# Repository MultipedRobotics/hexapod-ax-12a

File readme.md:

# Hexapod

*in process*

## Others

- Kevin Ochs [ROS1 Hexapod](https://github.com/KevinOchs/hexapod_ros)
    - 
- Razbotics [ROS1 Hexapod](https://github.com/Razbotics/hexapod_ros)
    - This is a fork of Kevin Ochs' hexapod
    - 
- Emiliano Borghi [ROS1 Crab](https://github.com/eborghi10/Hexapod-ROS)
- Biriuk Ivan [ROS1 Crab](http://wiki.ros.org/Robots/HexapodRobot)
    - 
- Davis Weis [ROS1 Hopper](https://github.com/dmweis/Hopper_ROS)
    - 
- Unknown 
    - 

# MIT License

**Copyright (c) 2020 Kevin J. Walchko**

Permission is hereby granted, free of charge, to any person obtaining a copy
of this software and associated documentation files (the "Software"), to deal
in the Software without restriction, including without limitation the rights
to use, copy, modify, merge, publish, distribute, sublicense, and/or sell
copies of the Software, and to permit persons to whom the Software is
furnished to do so, subject to the following conditions:

The above copyright notice and this permission notice shall be included in all
copies or substantial portions of the Software.

THE SOFTWARE IS PROVIDED "AS IS", WITHOUT WARRANTY OF ANY KIND, EXPRESS OR
IMPLIED, INCLUDING BUT NOT LIMITED TO THE WARRANTIES OF MERCHANTABILITY,
FITNESS FOR A PARTICULAR PURPOSE AND NONINFRINGEMENT. IN NO EVENT SHALL THE
AUTHORS OR COPYRIGHT HOLDERS BE LIABLE FOR ANY CLAIM, DAMAGES OR OTHER
LIABILITY, WHETHER IN AN ACTION OF CONTRACT, TORT OR OTHERWISE, ARISING FROM,
OUT OF OR IN CONNECTION WITH THE SOFTWARE OR THE USE OR OTHER DEALINGS IN THE
SOFTWARE.

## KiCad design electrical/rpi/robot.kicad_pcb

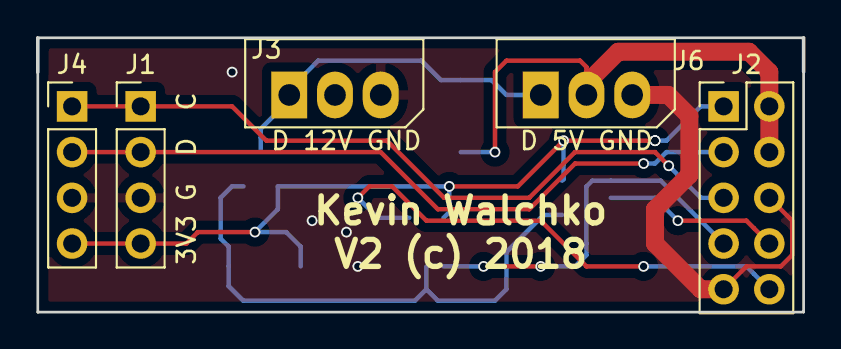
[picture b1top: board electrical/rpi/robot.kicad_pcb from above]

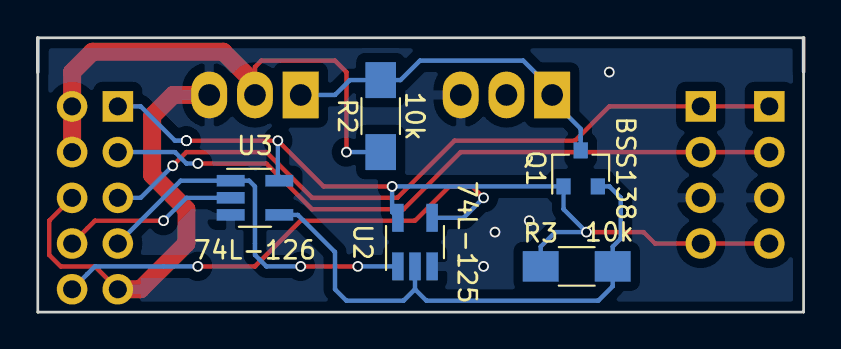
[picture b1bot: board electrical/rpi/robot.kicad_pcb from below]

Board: 2 copper layers, 42.5 x 15.2 mm, 10 parts (5 on the bottom side), 10 nets.

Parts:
J1, J4: i2c; Pin_Header_Straight_1x04_Pitch2.54mm
J2: Pi Header; Pin_Header_Straight_2x05_Pitch2.54mm
J3: 12V/Data; Molex_SPOX-5267_22-03-5035_03x2.54mm_Straight
J6: 5V/Data; Molex_SPOX-5267_22-03-5035_03x2.54mm_Straight
Q1: BSS138; SOT-23
R2, R3: 10k; R_1206_HandSoldering
U2: 74L-125; SOT-23-5_HandSoldering
U3: 74L-126; SOT-23-5_HandSoldering

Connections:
+3V3: J1.4, J2.1, J4.4, Q1.1, R3.1, U2.5, U3.5
+5V: J2.2, J2.4, J6.2, R2.1
DATA: J3.1, J6.1, Q1.3, R2.2
DTR: J2.7, U2.1, U3.1
GND: J1.3, J2.6, J2.9, J3.3, J4.3, J6.3, U2.3, U3.3
unnamed: Q1.2, R3.2, U2.2, U3.4
RXI: J2.10, U2.4
SCL: J1.1, J2.5, J4.1
SDA: J1.2, J2.3, J4.2
TXO: J2.8, U3.2

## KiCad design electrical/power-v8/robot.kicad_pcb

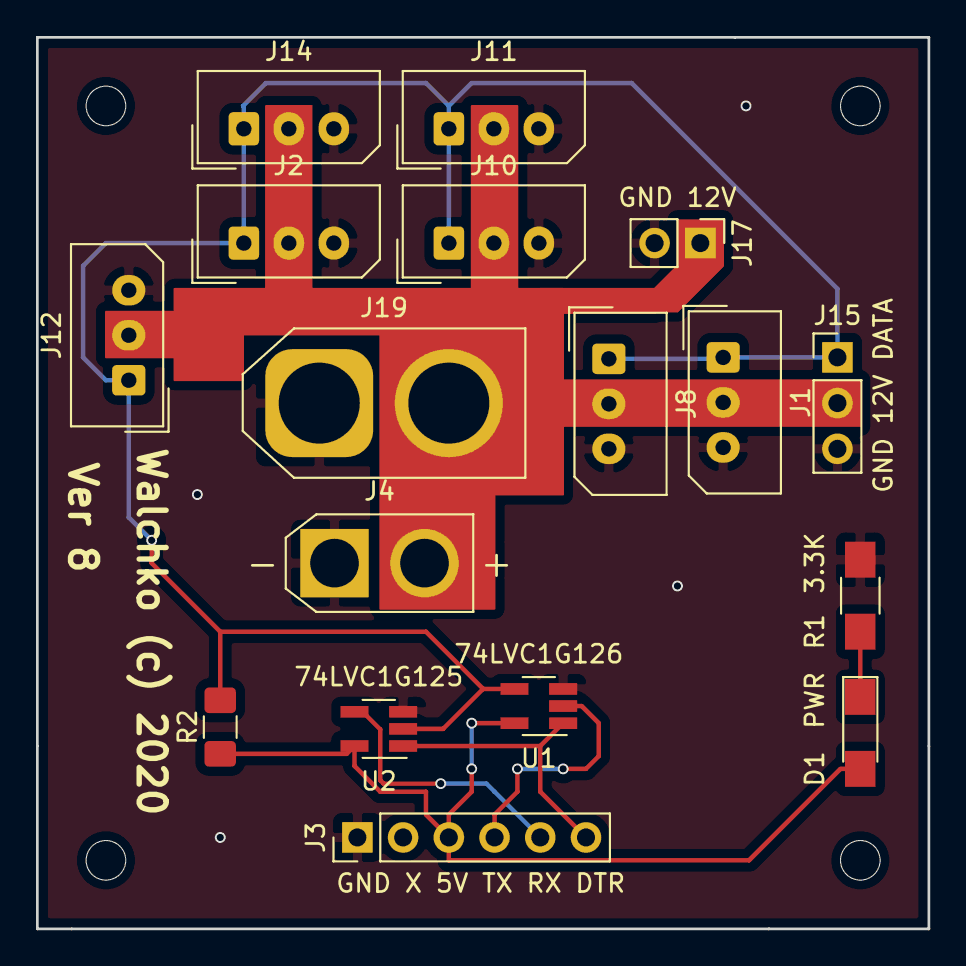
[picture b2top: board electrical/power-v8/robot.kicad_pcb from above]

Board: 2 copper layers, 49.5 x 49.5 mm, 22 parts (1 on the bottom side), 8 nets.

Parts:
 : MountingHole; MountingHole_2.2mm_M2_DIN965
 #2,  #3,  #4: MountingHole; MountingHole_2.2mm_M2_DIN965
D1: PWR; LED_1206_HandSoldering
J1: LEG1; Molex_SPOX_5267-03A_1x03_P2.50mm_Vertical
J2: LEG5; Molex_SPOX_5267-03A_1x03_P2.50mm_Vertical
J3: Conn_01x06; PinHeader_1x06_P2.54mm_Vertical
J4: XT30; AMASS_XT30U-M_1x02_P5.0mm_Vertical
J8: LEG2; Molex_SPOX_5267-03A_1x03_P2.50mm_Vertical
J10: LEG3; Molex_SPOX_5267-03A_1x03_P2.50mm_Vertical
J11: LEG4; Molex_SPOX_5267-03A_1x03_P2.50mm_Vertical
J12: EXTRA; Molex_SPOX_5267-03A_1x03_P2.50mm_Vertical
J14: LEG6; Molex_SPOX_5267-03A_1x03_P2.50mm_Vertical
J15: EXTRA; PinHeader_1x03_P2.54mm_Vertical
J17: 12V; Pin_Header_Straight_1x02_Pitch2.54mm
J19: XT60; AMASS_XT60-M_1x02_P7.20mm_Vertical
LOGO1: Logo_Open_Hardware_Large; OSHW-Logo2_24.3x20mm_SilkScreen
R1: 3.3K; R_1206_HandSoldering
R2: 10K; R_1206_3216Metric_Pad1.42x1.75mm_HandSolder
U1: 74LVC1G126; SOT-23-5_HandSoldering
U2: 74LVC1G125; SOT-23-5_HandSoldering

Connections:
+5V: D1.2, J3.3, R2.1, U1.5, U2.5
+12V: J1.2, J2.2, J4.2, J8.2, J10.2, J11.2, J12.2, J14.2, J15.2, J17.1, J19.2
DATA: J1.1, J2.1, J8.1, J10.1, J11.1, J12.1, J14.1, J15.1, R2.2, U1.4, U2.2
DTR: J3.6, U1.1, U2.1
GND: J1.3, J2.3, J3.1, J4.1, J8.3, J10.3, J11.3, J12.3, J14.3, J15.3, J17.2, J19.1, R1.2, U1.3, U2.3
unnamed: D1.1, R1.1
RX: J3.5, U2.4
TX: J3.4, U1.2

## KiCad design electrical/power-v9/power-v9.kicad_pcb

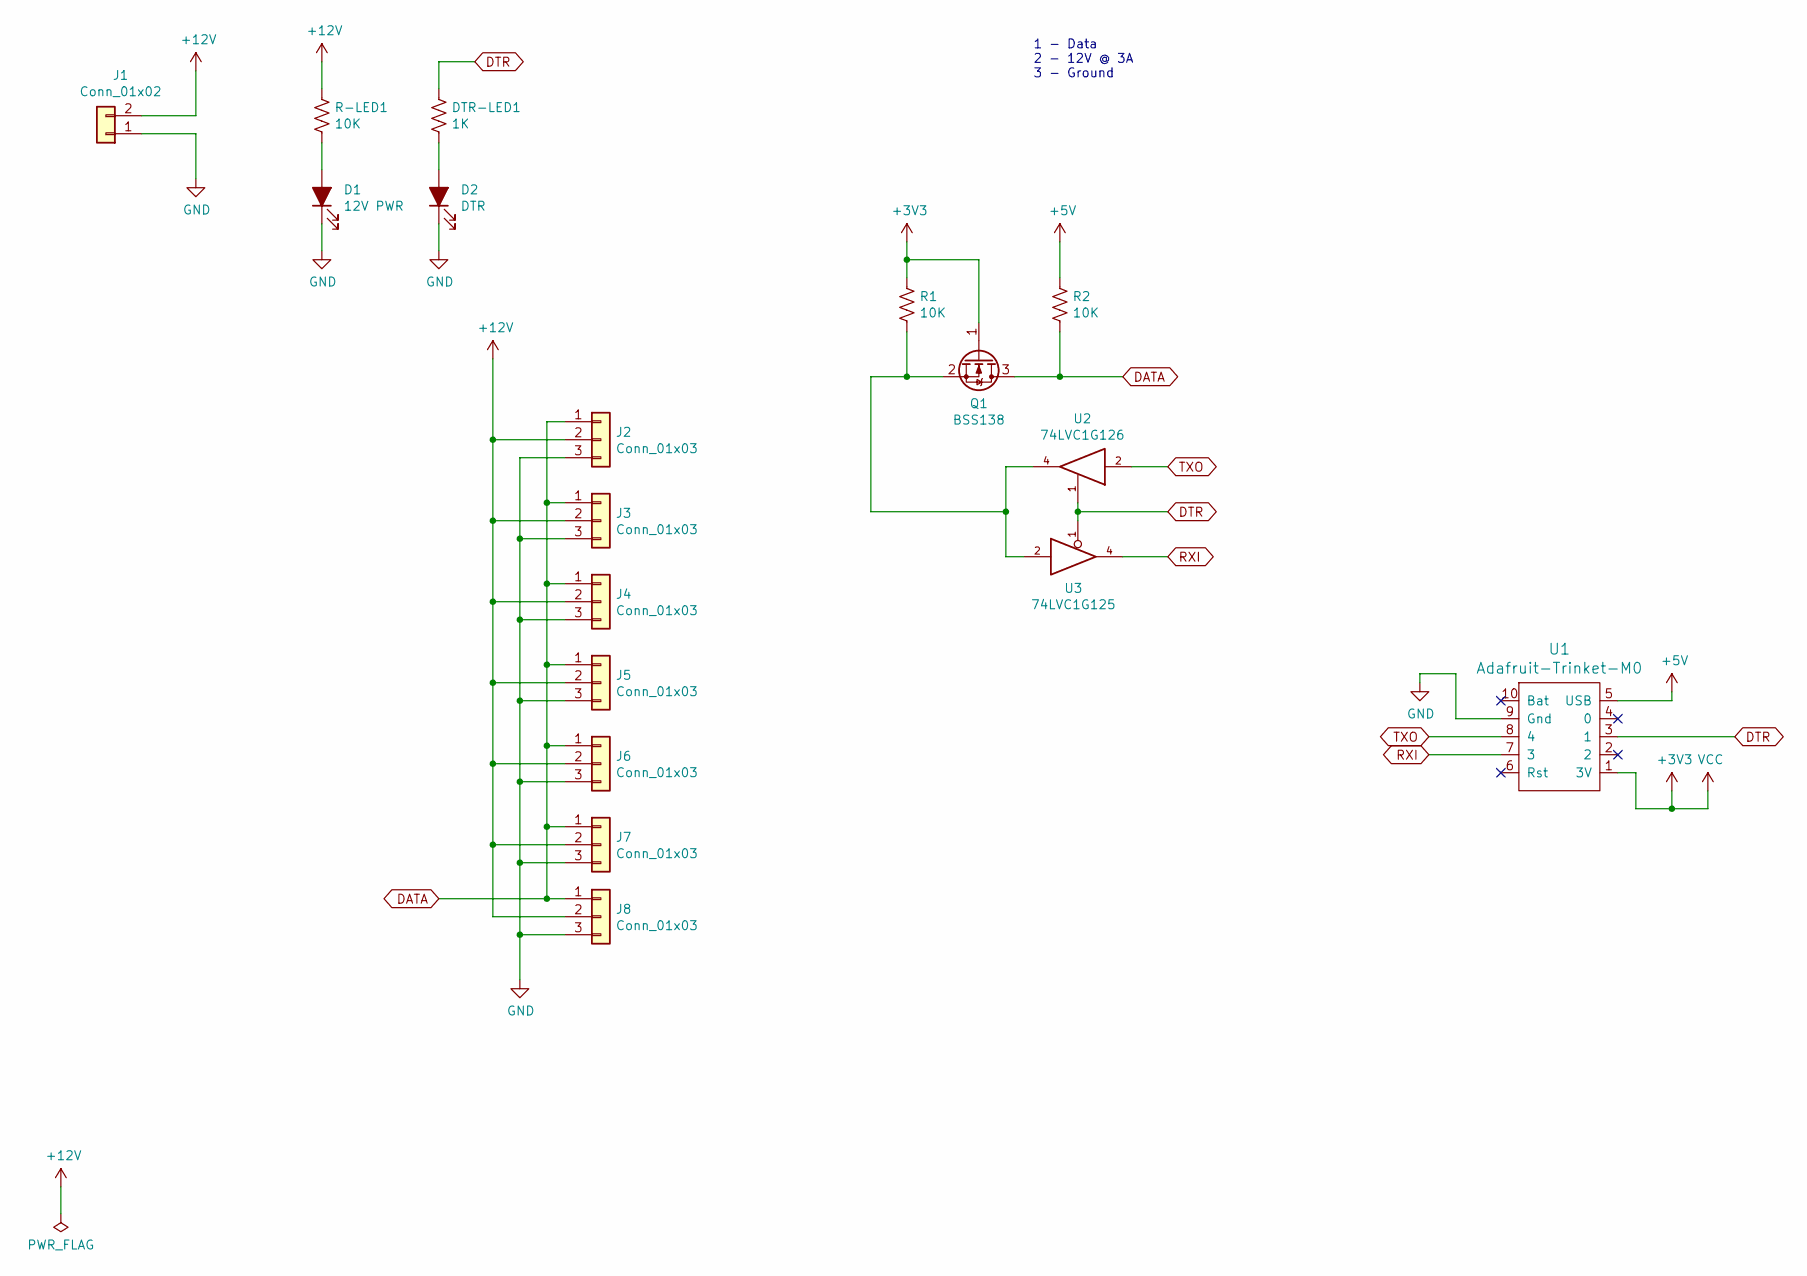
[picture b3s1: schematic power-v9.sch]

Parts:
D1: 12V PWR; LED_1206_3216Metric_Pad1.42x1.75mm_HandSolder
D2: DTR; LED_1206_3216Metric_Pad1.42x1.75mm_HandSolder
DTR-LED1: 1K; R_0603_1608Metric_Pad0.98x0.95mm_HandSolder
J1: Conn_01x02; AMASS_XT60-M_1x02_P7.20mm_Vertical
J2, J3, J4, J5, J6, J7, J8: Conn_01x03; Molex_SPOX_5267-03A_1x03_P2.50mm_Vertical
Q1: BSS138; SOT-23
R1, R2: 10K; R_0603_1608Metric_Pad0.98x0.95mm_HandSolder
R-LED1: 10K; R_0603_1608Metric_Pad0.98x0.95mm_HandSolder
U1: Adafruit-Trinket-M0; adafruit-trinket-m0
U2: 74LVC1G126; SOT-23-5_HandSoldering
U3: 74LVC1G125; SOT-23-5_HandSoldering

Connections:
+3V3: Q1.1 (G), R1.1, U1.1 (3V), U2.5 (VCC), U3.5 (VCC)
+5V: R2.1, U1.5 (USB)
+12V: J1.2, J2.2, J3.2, J4.2, J5.2, J6.2, J7.2, J8.2, R-LED1.1
DATA: J2.1, J3.1, J4.1, J5.1, J6.1, J7.1, J8.1, Q1.3 (D), R2.2
DTR: DTR-LED1.1, U1.3 (1), U2.1, U3.1
GND: D1.1 (K), D2.1 (K), J1.1, J2.3, J3.3, J4.3, J5.3, J6.3, J7.3, J8.3, U1.9 (Gnd), U2.3 (GND), U3.3 (GND)
unnamed: D1.2 (A), R-LED1.2
unnamed: D2.2 (A), DTR-LED1.2
unnamed: Q1.2 (S), R1.2, U2.4, U3.2
RXI: U1.7 (3), U3.4
TXO: U1.8 (4), U2.2

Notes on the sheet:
1 - Data 2 - 12V @ 3A 3 - Ground

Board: 2 copper layers, 18 parts (0 on the bottom side), 11 nets, no tracks yet.

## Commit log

2020-01-12 init
2020-01-17 update :robot: :bento:
2020-02-09 new foot :bento:
2020-02-09 fix width to 24 mm :bento:

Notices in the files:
electrical/power-v8/robot.kicad_pcb:
Walchko (c) 2020
electrical/rpi/robot.kicad_pcb:
V2 (c) 2018
